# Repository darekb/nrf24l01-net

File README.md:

#branch test01

in this branch i test comunication via different pipe for each sensors.

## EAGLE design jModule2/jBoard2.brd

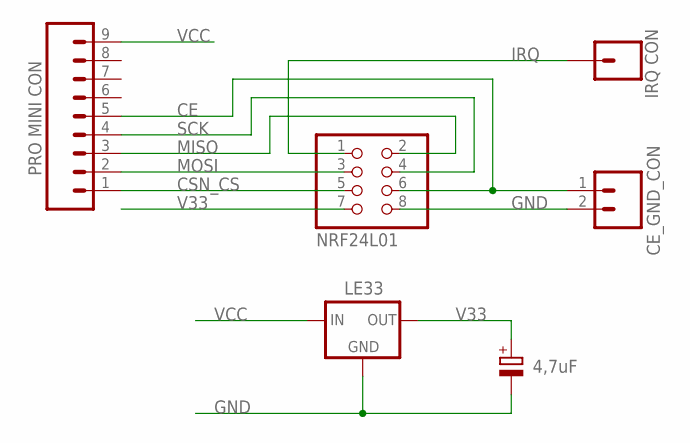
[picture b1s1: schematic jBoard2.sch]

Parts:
C3: 4,7uF; E2-5
IC1: LE33; 78LXX
J1: PRO MINI CON; 1X09
J2: IRQ CON; 1X01
J3: CE_GND_CON; 1X02
JP2: NRF24L01; 2X04

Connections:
CE: J1.5, J3.1, JP2.6
CSN_CS: J1.1, JP2.5
GND: C3.-, IC1.GND, J3.2, JP2.8
IRQ: J2.1, JP2.1
MISO: J1.3, JP2.2
MOSI: J1.2, JP2.3
SCK: J1.4, JP2.4
V33: C3.+, IC1.OUT, JP2.7
VCC: IC1.IN, J1.9

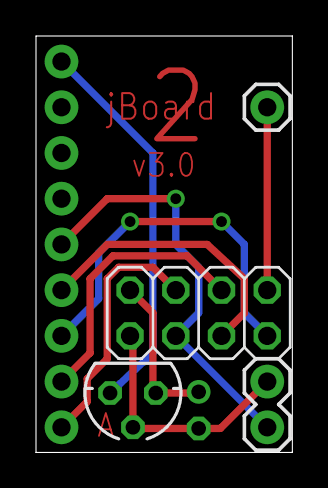
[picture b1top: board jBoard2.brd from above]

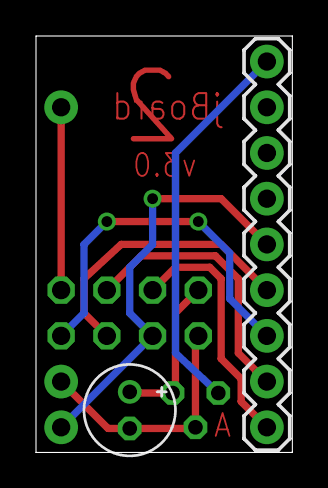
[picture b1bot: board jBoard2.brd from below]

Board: 2 copper layers, 14.2 x 23.1 mm, 6 parts (2 on the bottom side), 9 nets.

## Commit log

2017-05-07 start
2017-05-07 add readme
2017-05-09 workin solution (not very well but ok)
2017-05-10 working solutiion 1 pipe differents adresses
2017-05-10 workin solution
2017-05-11 all it is ok
2017-05-12 more tests
2017-05-24 working solution
2017-05-31 all ok
2017-06-01 remove float to decrease kode size
2017-06-24 new version with atmega8 as sensors and atmega328 as server
2017-07-07 propably work (not tested)
2017-10-31 change nrf24 conigurartion
2018-01-02 a lot changes
2018-01-03 working solution (get measurements, reset after 3 fails, get data from server)
2018-01-04 new version of server and sensor21
2018-01-05 add circuit scheme and pcb project in KiCad
2018-01-16 łączy co dugie wywołanie
2018-01-16 clean code
2018-01-16 after cleaning code
2018-01-17 test
2018-01-17 asdf
2018-01-22 some changes
2018-01-23 add interupt on error sending data from NRF24L01
2018-01-23 sme changes
2018-01-23 nic nie działa
2018-01-24 działa co drugie wysłanie
2018-01-24 test01
2018-01-29 not work
2018-01-29 log file
2018-01-29 workin partly
2018-02-01 working almost well
2018-02-02 clean some code
2018-02-05 all works ok
2018-02-07 server side work fine
2018-02-08 all worl well
2018-02-15 all work well
2018-02-19 add slPCF8563.c slPCF8563.h and registers mnemonics
2018-02-19 add controls status bits mnemonics
2018-02-19 library PCF8563 writed but not tested yet
2018-02-20 some mesurements
2019-04-04 before big changes

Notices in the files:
parts and their libraries:
SparkFun-Connectors: Licensing: Creative Commons ShareAlike 4.0 International - https://creativecommons.org/licenses/by-sa/4.0
